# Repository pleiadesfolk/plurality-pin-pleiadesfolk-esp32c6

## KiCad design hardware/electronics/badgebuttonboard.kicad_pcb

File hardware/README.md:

# Hardware

| Folder | What's in it |
| --- | --- |
| `electronics/` | The button daughterboard (`badgebuttonboard`): KiCad project, Gerbers, drill files, BOM and placement files for JLCPCB |
| `mechanical/` | The desk stand (base, lever, cable holder) and casing files as `.3mf`.  |

## Casing

Two versions of the case are available, one with buttons and one without. 
Recommended layer height is 0.2mm, with PLA supports if printed in PETG.
If printing with a transparent filament, please follow the settings at 
https://www.printables.com/model/15310-how-to-print-glass
One M2x5 and two M2x10 screws are required for assembly if you are using the 
button daughterboard, else three M2x5 screws are required. When securing the 
PCB assembly with the button daughterboard into the case, some tweaking of 
screw tightness may be required to ensure that the top button is able to 
actuate, and as a result the lower left corner might protrude a bit.

## Button daughterboard

Two buttons and an RGB LED, connected to the dev board by two connectors.
Green and blue aren't connected because the dev board has no free GPIOs left.
GPIO2, 3 and 6 are the only free pins once GPIO9 stays the BOOT button.

The button board is designed to be fabricated at JLCPCB with a 0.8mm thick
PCB, all other settings remaining as default. Select the option for PCB 
assembly, and use badgebuttonboard.csv and badgebuttonboard-all-pos.csv for 
BOM and part placement files respectively.

**GPIO23 can't be used**, although it's on header P2: the dev board wires it
to the display's tearing-effect output (`OLED_TE`, through the 0 Ω link R3),
which drives the line itself. Solder the board as shown in the image. 

With reference to the image, the top rightmost pin on the daughterboard should 
be soldered to GPIO6, with the pin to the left of it soldered to GPIO3. The
3V3, GND, and GPIO2 pins should be soldered with headers for mechanical support.

## Stand

All the stand parts are designed to print without support. The stand is designed 
to use four 8x3mm button magnets, but the cavity is 5mm deep to allow tuning of 
the magnet depth for magnets of different strength. Use superglue to secure the 
position of the magnet. The ejection lever is intended to be pinned into the 
stand with a length of 1.75mm filament, through the channel shown below.

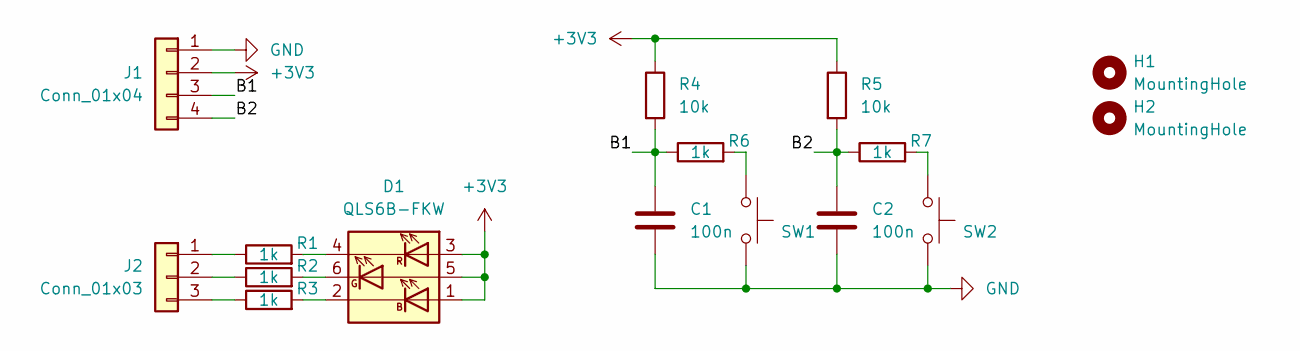
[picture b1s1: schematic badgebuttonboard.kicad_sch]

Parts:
C1, C2: 100n; C_0402_1005Metric
D1: QLS6B-FKW; LED_Cree-PLCC6_4.7x1.5mm
H1, H2: MountingHole; MountingHole_2.2mm_M2
J1: Conn_01x04; PinHeader_1x04_P2.54mm_Vertical
J2: Conn_01x03; PinHeader_1x03_P2.54mm_Vertical
R1, R2, R3, R6, R7: 1k; R_0402_1005Metric
R4, R5: 10k; R_0402_1005Metric
SW1, SW2: SW_Push; SW-SMD_2P-TS24CA

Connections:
+3V3: D1.1 (AB), D1.3 (AR), D1.5 (AG), J1.2, R4.1, R5.1
/B1: C1.1, J1.3, R4.2, R6.1
/B2: C2.1, J1.4, R5.2, R7.1
GND: C1.2, C2.2, J1.1, SW1.1, SW1.3 (1), SW1.4 (1), SW2.1, SW2.3 (1), SW2.4 (1)
unnamed: D1.2 (KB), R3.2
unnamed: D1.4 (KR), R1.2
unnamed: D1.6 (KR), R2.2
unnamed: J2.1, R1.1
unnamed: J2.2, R2.1
unnamed: J2.3, R3.1
unnamed: R6.2, SW1.2
unnamed: R7.2, SW2.2

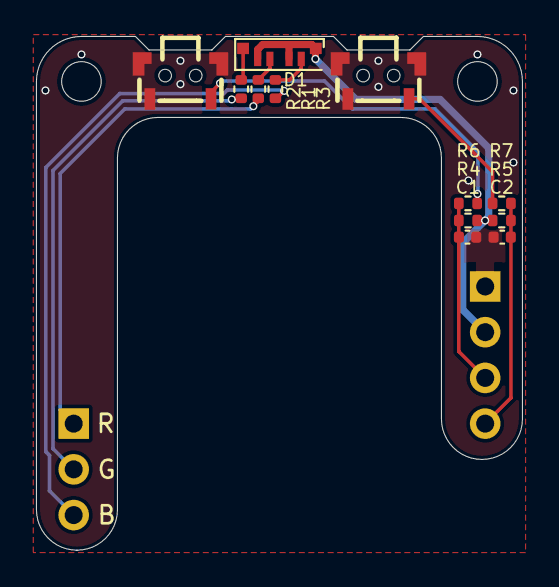
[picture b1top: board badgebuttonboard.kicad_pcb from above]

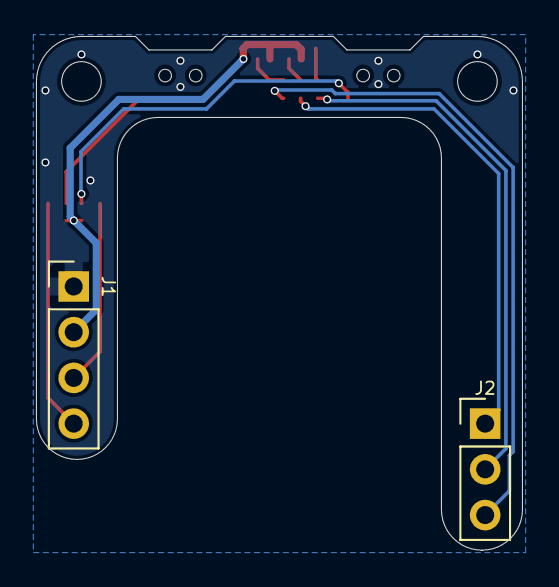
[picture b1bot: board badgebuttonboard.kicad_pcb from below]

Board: 2 copper layers, 27.0 x 28.5 mm, 16 parts (2 on the bottom side), 12 nets.
